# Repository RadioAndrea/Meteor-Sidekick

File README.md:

# Meteor-Sidekick
Slide out keyboard for modern smartphones

Uses Nice!Nano as a microcontroller and the first implementation is sized to a Pixel 7 Pro

Current implementation is with the Kailh Scissor switches as they are very thin and available unlike the ultramecs 6c switches.

If you know of a way to get thinner mechanical switches, like the Ultramecs, at a reasonable price (not $150 a board), please raise an issue in this repo.

# Project Status
## November 2022
Boards that were created were milled with the wrong size of drill bit due to board fab error.
Fabricator remade boards to rectify this.

## January 2023
New boards arrived and components are still being collected.

## Jul 2023
Solder paste stencil arrived and reflow oven was obtained.
Soldering of transistors will happen by paste and reflow, while switches will be done entirely by hand.

## Jan 2024
Board has been produced and now soldered thanks to my steady handed assistant.

# Images
## Real Photographs
### SMD Soldering

### Adding Switches and Caps

### Praise the manufacturing tolerances

## 2D Drawing

## 3D Render
### Front

### Back

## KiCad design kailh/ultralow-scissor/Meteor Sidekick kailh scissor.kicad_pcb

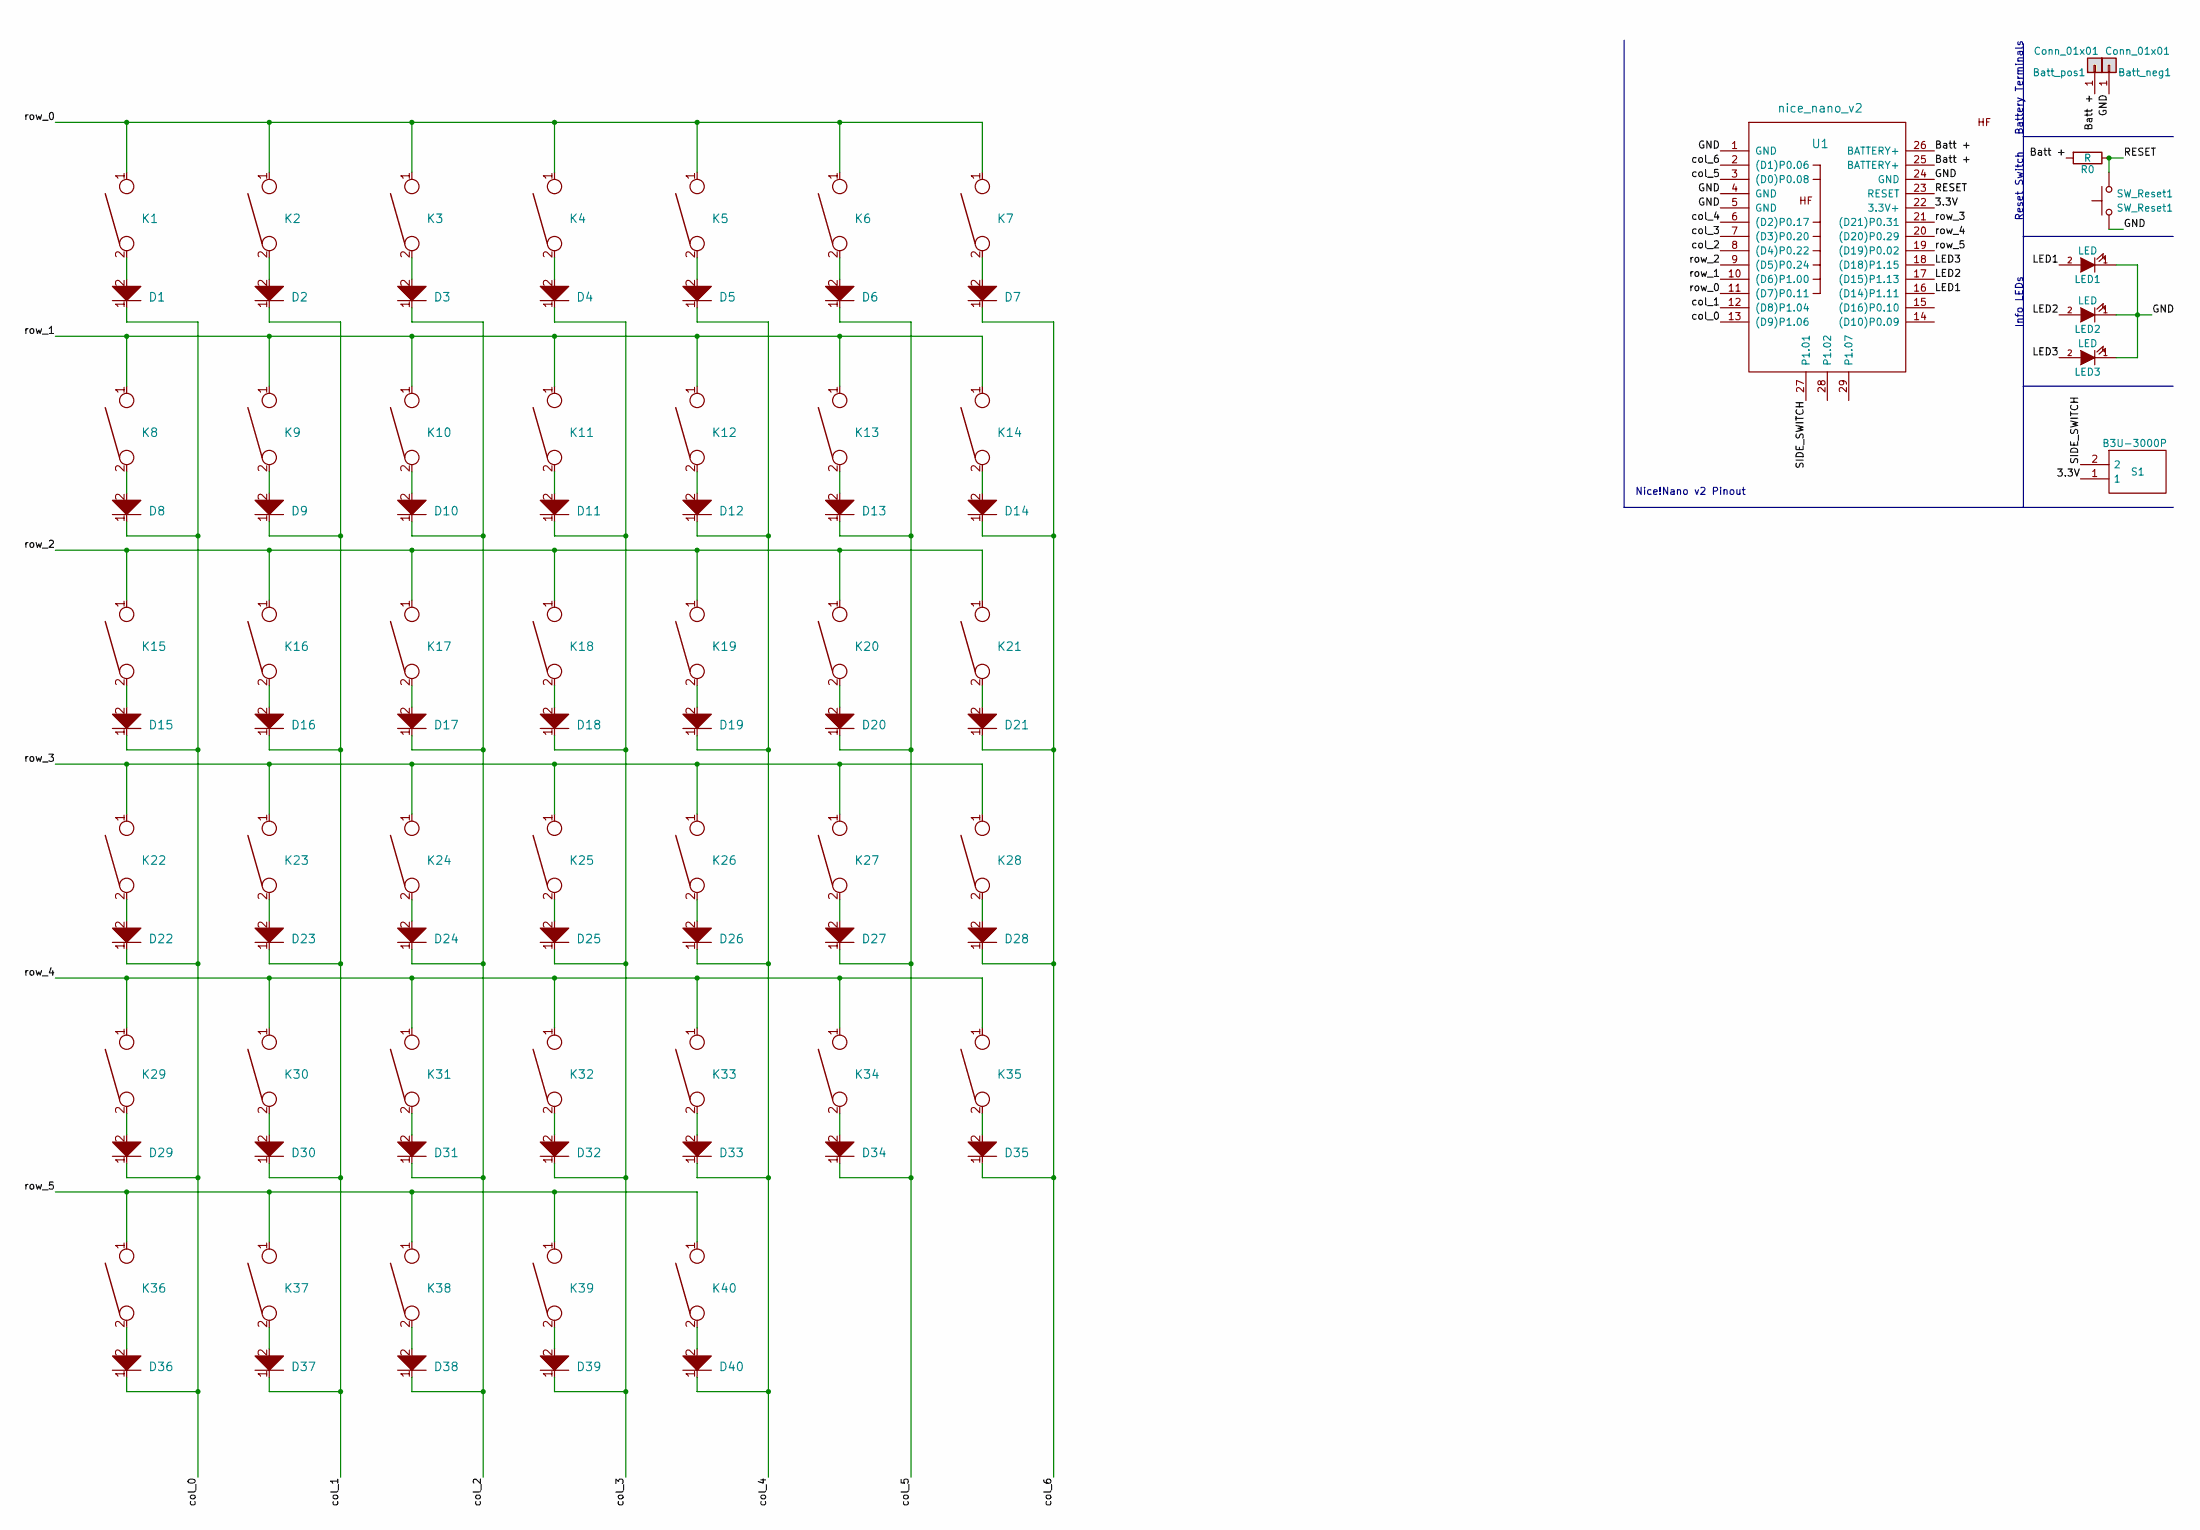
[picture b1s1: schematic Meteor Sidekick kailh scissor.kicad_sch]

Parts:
Batt_neg1: Conn_01x01; SolderWire-0.1sqmm_1x01_D0.4mm_OD1mm
Batt_pos1: Conn_01x01; SolderWire-0.1sqmm_1x01_D0.4mm_OD1mm
D1, D2, D3, D4, D5, D6, D7, D8, D9, D10, D11, D12, D13, D14, D15, D16, D17, D18, D19, D20, D21, D22, D23, D24, D25, D26, D27, D28, D29, D30, D31, D32, D33, D34, D35, D36, D37, D38, D39, D40: D; D_0805_2012Metric
K1, K2, K3, K4, K5, K6, K7, K8, K9, K10, K11, K12, K13, K14, K15, K16, K17, K18, K19, K20, K21, K22, K23, K24, K25, K26, K27, K28, K29, K30, K31, K32, K33, K34, K35, K36, K37, K38, K39, K40: KEYSW; Kailh-PG1425-X-Switch
LED1, LED2, LED3: LED; LED_0805_2012Metric
R0: R; R_0805_2012Metric
S1: B3U-3000P; B3U-1000P; Mouser Part Number 653-B3U-3000P
SW_Reset1: SW_Reset1; SolderJumper-2_P1.3mm_Open_Pad1.0x1.5mm
U1: nice_nano_v2

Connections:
/3.3V: S1.1, U1.22 (3.3V+)
/Batt +: Batt_pos1.1, R0.2, U1.25 (BATTERY+), U1.26 (BATTERY+)
/GND: Batt_neg1.1, LED1.1 (K), LED2.1 (K), LED3.1 (K), SW_Reset1.1, U1.1 (GND), U1.4 (GND), U1.5 (GND), U1.24 (GND)
/LED1: LED1.2 (A), U1.16 ((D14)P1.11)
/LED2: LED2.2 (A), U1.17 ((D15)P1.13)
/LED3: LED3.2 (A), U1.18 ((D18)P1.15)
/RESET: R0.1, SW_Reset1.2, U1.23 (RESET)
/SIDE_SWITCH: S1.2, U1.27 (P1.01)
/col_0: D1.1, D8.1, D15.1, D22.1, D29.1, D36.1, U1.13 ((D9)P1.06)
/col_1: D2.1, D9.1, D16.1, D23.1, D30.1, D37.1, U1.12 ((D8)P1.04)
/col_2: D3.1, D10.1, D17.1, D24.1, D31.1, D38.1, U1.8 ((D4)P0.22)
/col_3: D4.1, D11.1, D18.1, D25.1, D32.1, D39.1, U1.7 ((D3)P0.20)
/col_4: D5.1, D12.1, D19.1, D26.1, D33.1, D40.1, U1.6 ((D2)P0.17)
/col_5: D6.1, D13.1, D20.1, D27.1, D34.1, U1.3 ((D0)P0.08)
/col_6: D7.1, D14.1, D21.1, D28.1, D35.1, U1.2 ((D1)P0.06)
/row_0: K1.1, K2.1, K3.1, K4.1, K5.1, K6.1, K7.1, U1.11 ((D7)P0.11)
/row_1: K8.1, K9.1, K10.1, K11.1, K12.1, K13.1, K14.1, U1.10 ((D6)P1.00)
/row_2: K15.1, K16.1, K17.1, K18.1, K19.1, K20.1, K21.1, U1.9 ((D5)P0.24)
/row_3: K22.1, K23.1, K24.1, K25.1, K26.1, K27.1, K28.1, U1.21 ((D21)P0.31)
/row_4: K29.1, K30.1, K31.1, K32.1, K33.1, K34.1, K35.1, U1.20 ((D20)P0.29)
/row_5: K36.1, K37.1, K38.1, K39.1, K40.1, U1.19 ((D19)P0.02)
unnamed: D1.2, K1.2
unnamed: D2.2, K2.2
unnamed: D3.2, K3.2
unnamed: D4.2, K4.2
unnamed: D5.2, K5.2
unnamed: D6.2, K6.2
unnamed: D7.2, K7.2
unnamed: D8.2, K8.2
unnamed: D9.2, K9.2
unnamed: D10.2, K10.2
unnamed: D11.2, K11.2
unnamed: D12.2, K12.2
unnamed: D13.2, K13.2
unnamed: D14.2, K14.2
unnamed: D15.2, K15.2
unnamed: D16.2, K16.2
unnamed: D17.2, K17.2
unnamed: D18.2, K18.2
unnamed: D19.2, K19.2
unnamed: D20.2, K20.2
unnamed: D21.2, K21.2
unnamed: D22.2, K22.2
unnamed: D23.2, K23.2
unnamed: D24.2, K24.2
unnamed: D25.2, K25.2
unnamed: D26.2, K26.2
unnamed: D27.2, K27.2
unnamed: D28.2, K28.2
unnamed: D29.2, K29.2
unnamed: D30.2, K30.2
unnamed: D31.2, K31.2
unnamed: D32.2, K32.2
unnamed: D33.2, K33.2
unnamed: D34.2, K34.2
unnamed: D35.2, K35.2
unnamed: D36.2, K36.2
unnamed: D37.2, K37.2
unnamed: D38.2, K38.2
unnamed: D39.2, K39.2
unnamed: D40.2, K40.2

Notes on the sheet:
Nice!Nano v2 Pinout
Battery Terminals
Reset Switch
Info LEDs

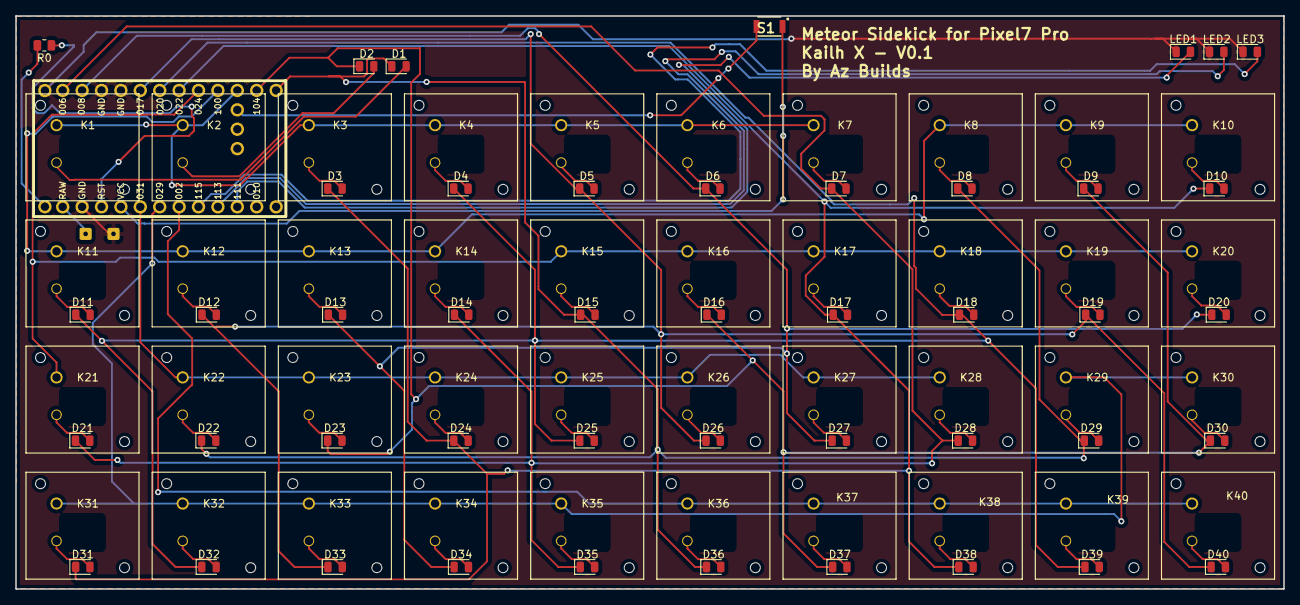
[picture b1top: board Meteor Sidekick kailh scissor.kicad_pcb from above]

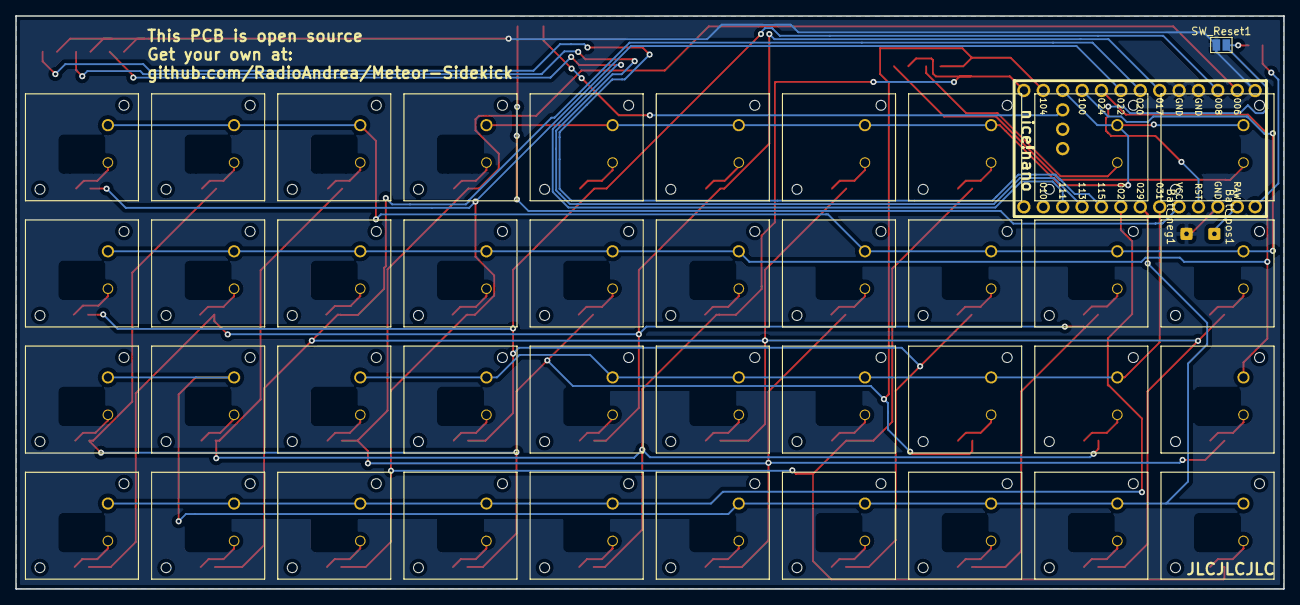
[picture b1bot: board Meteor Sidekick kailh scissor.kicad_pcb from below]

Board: 2 copper layers, 166.0 x 75.0 mm, 89 parts (4 on the bottom side), 61 nets.

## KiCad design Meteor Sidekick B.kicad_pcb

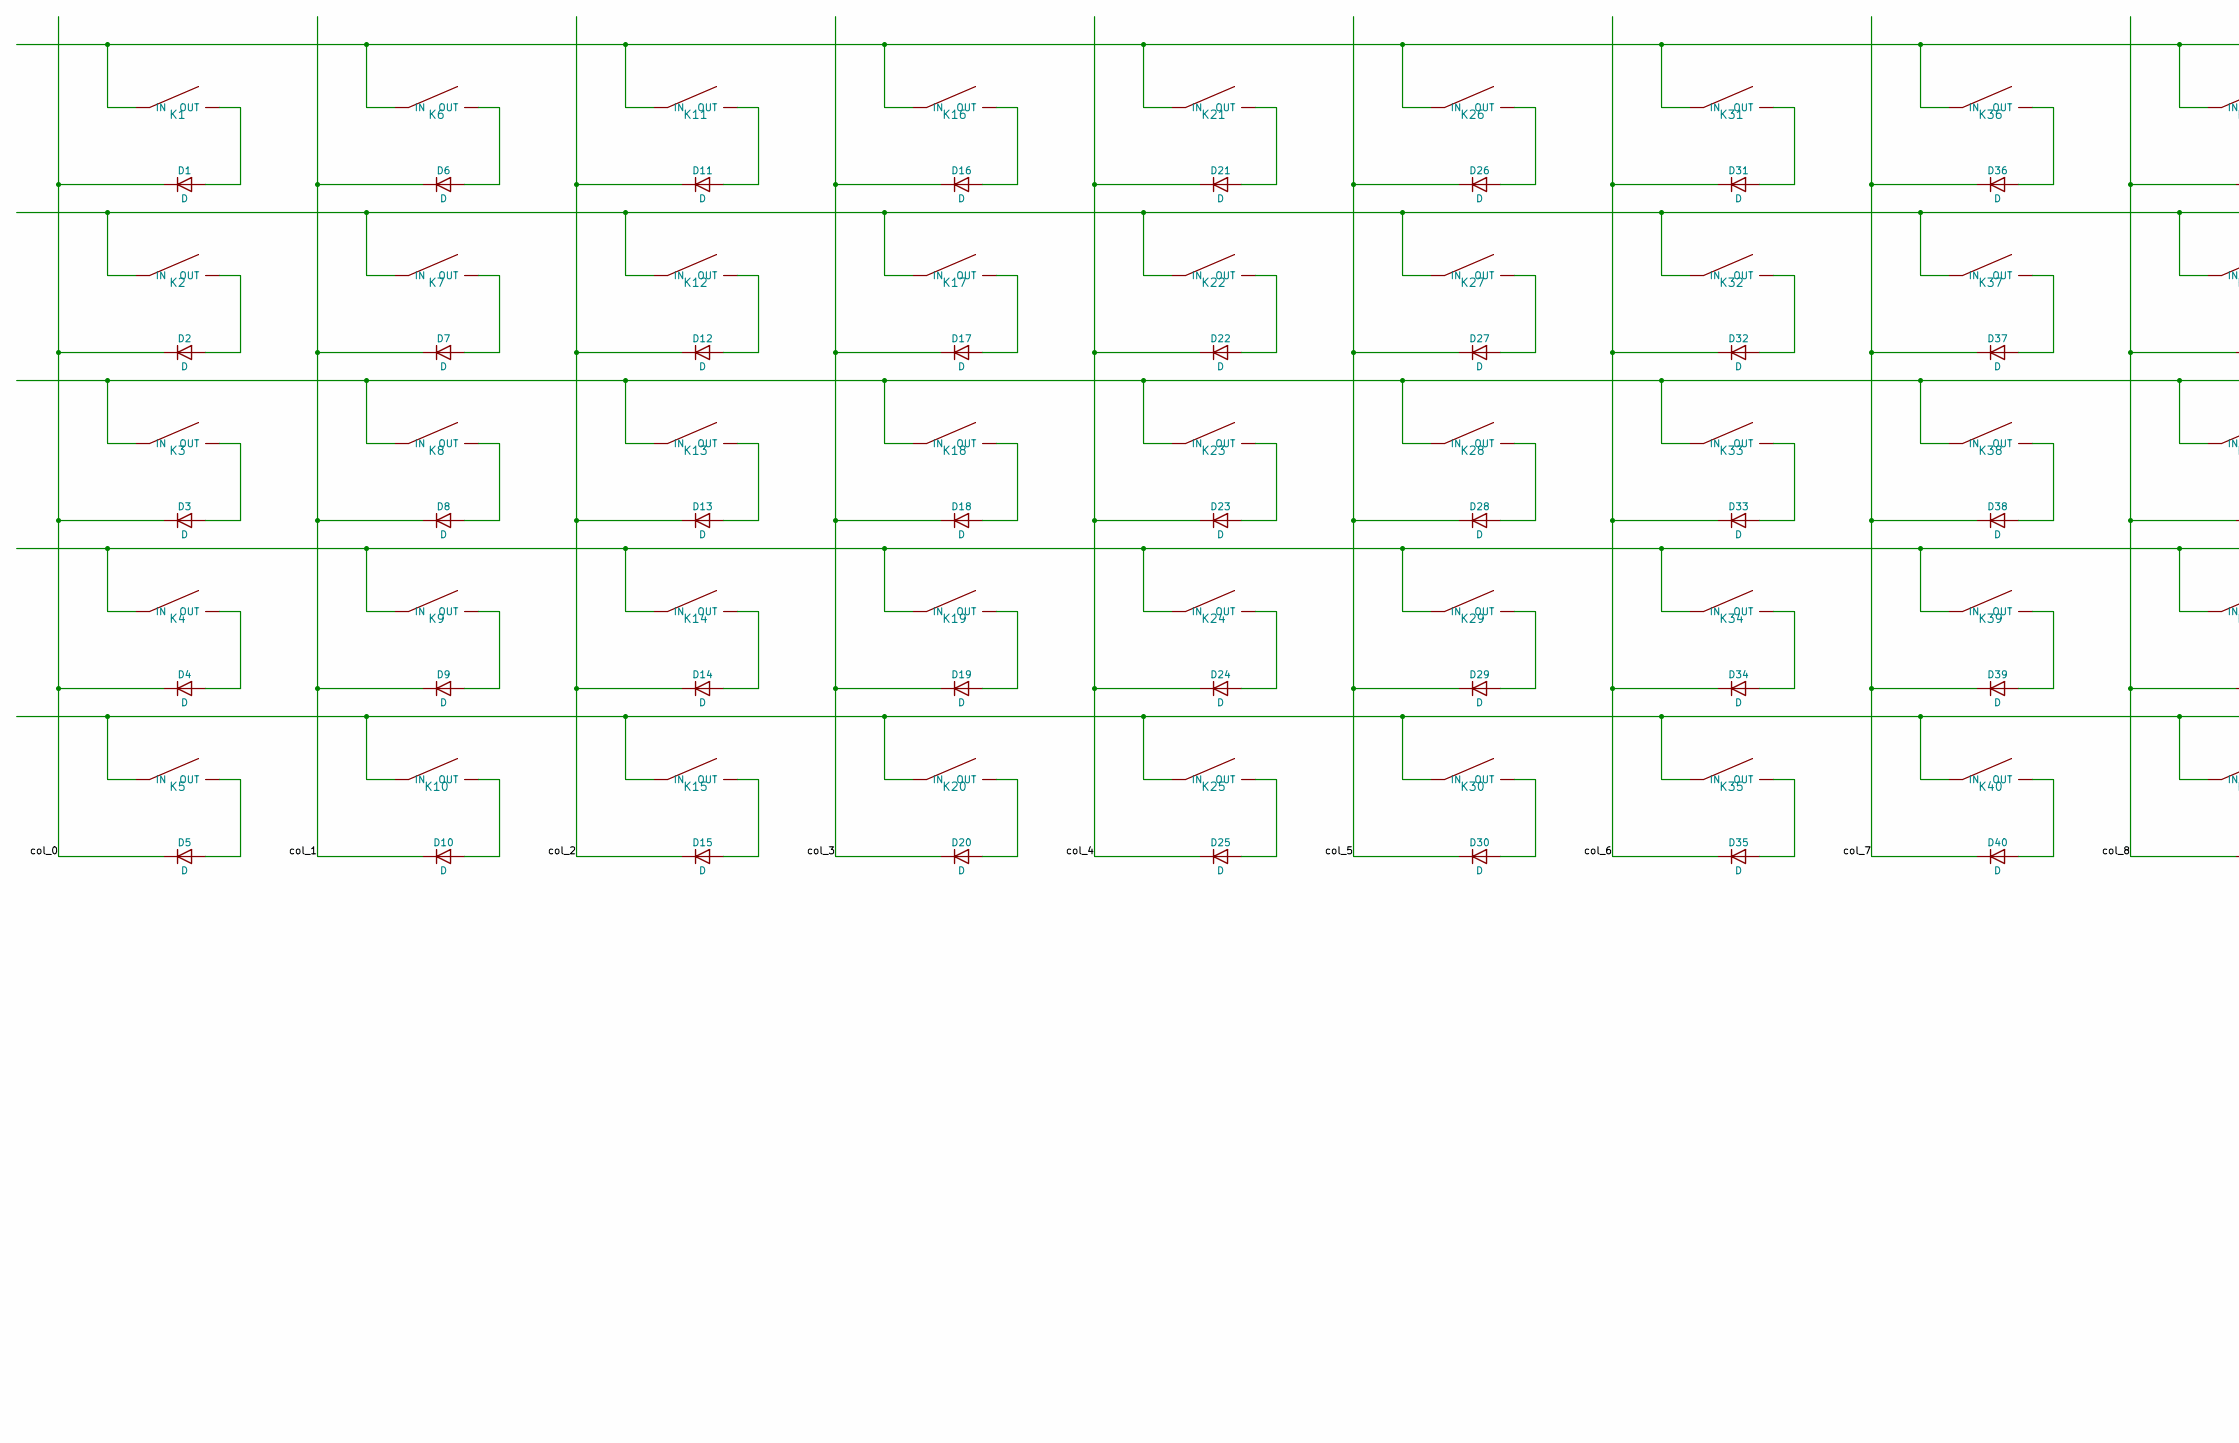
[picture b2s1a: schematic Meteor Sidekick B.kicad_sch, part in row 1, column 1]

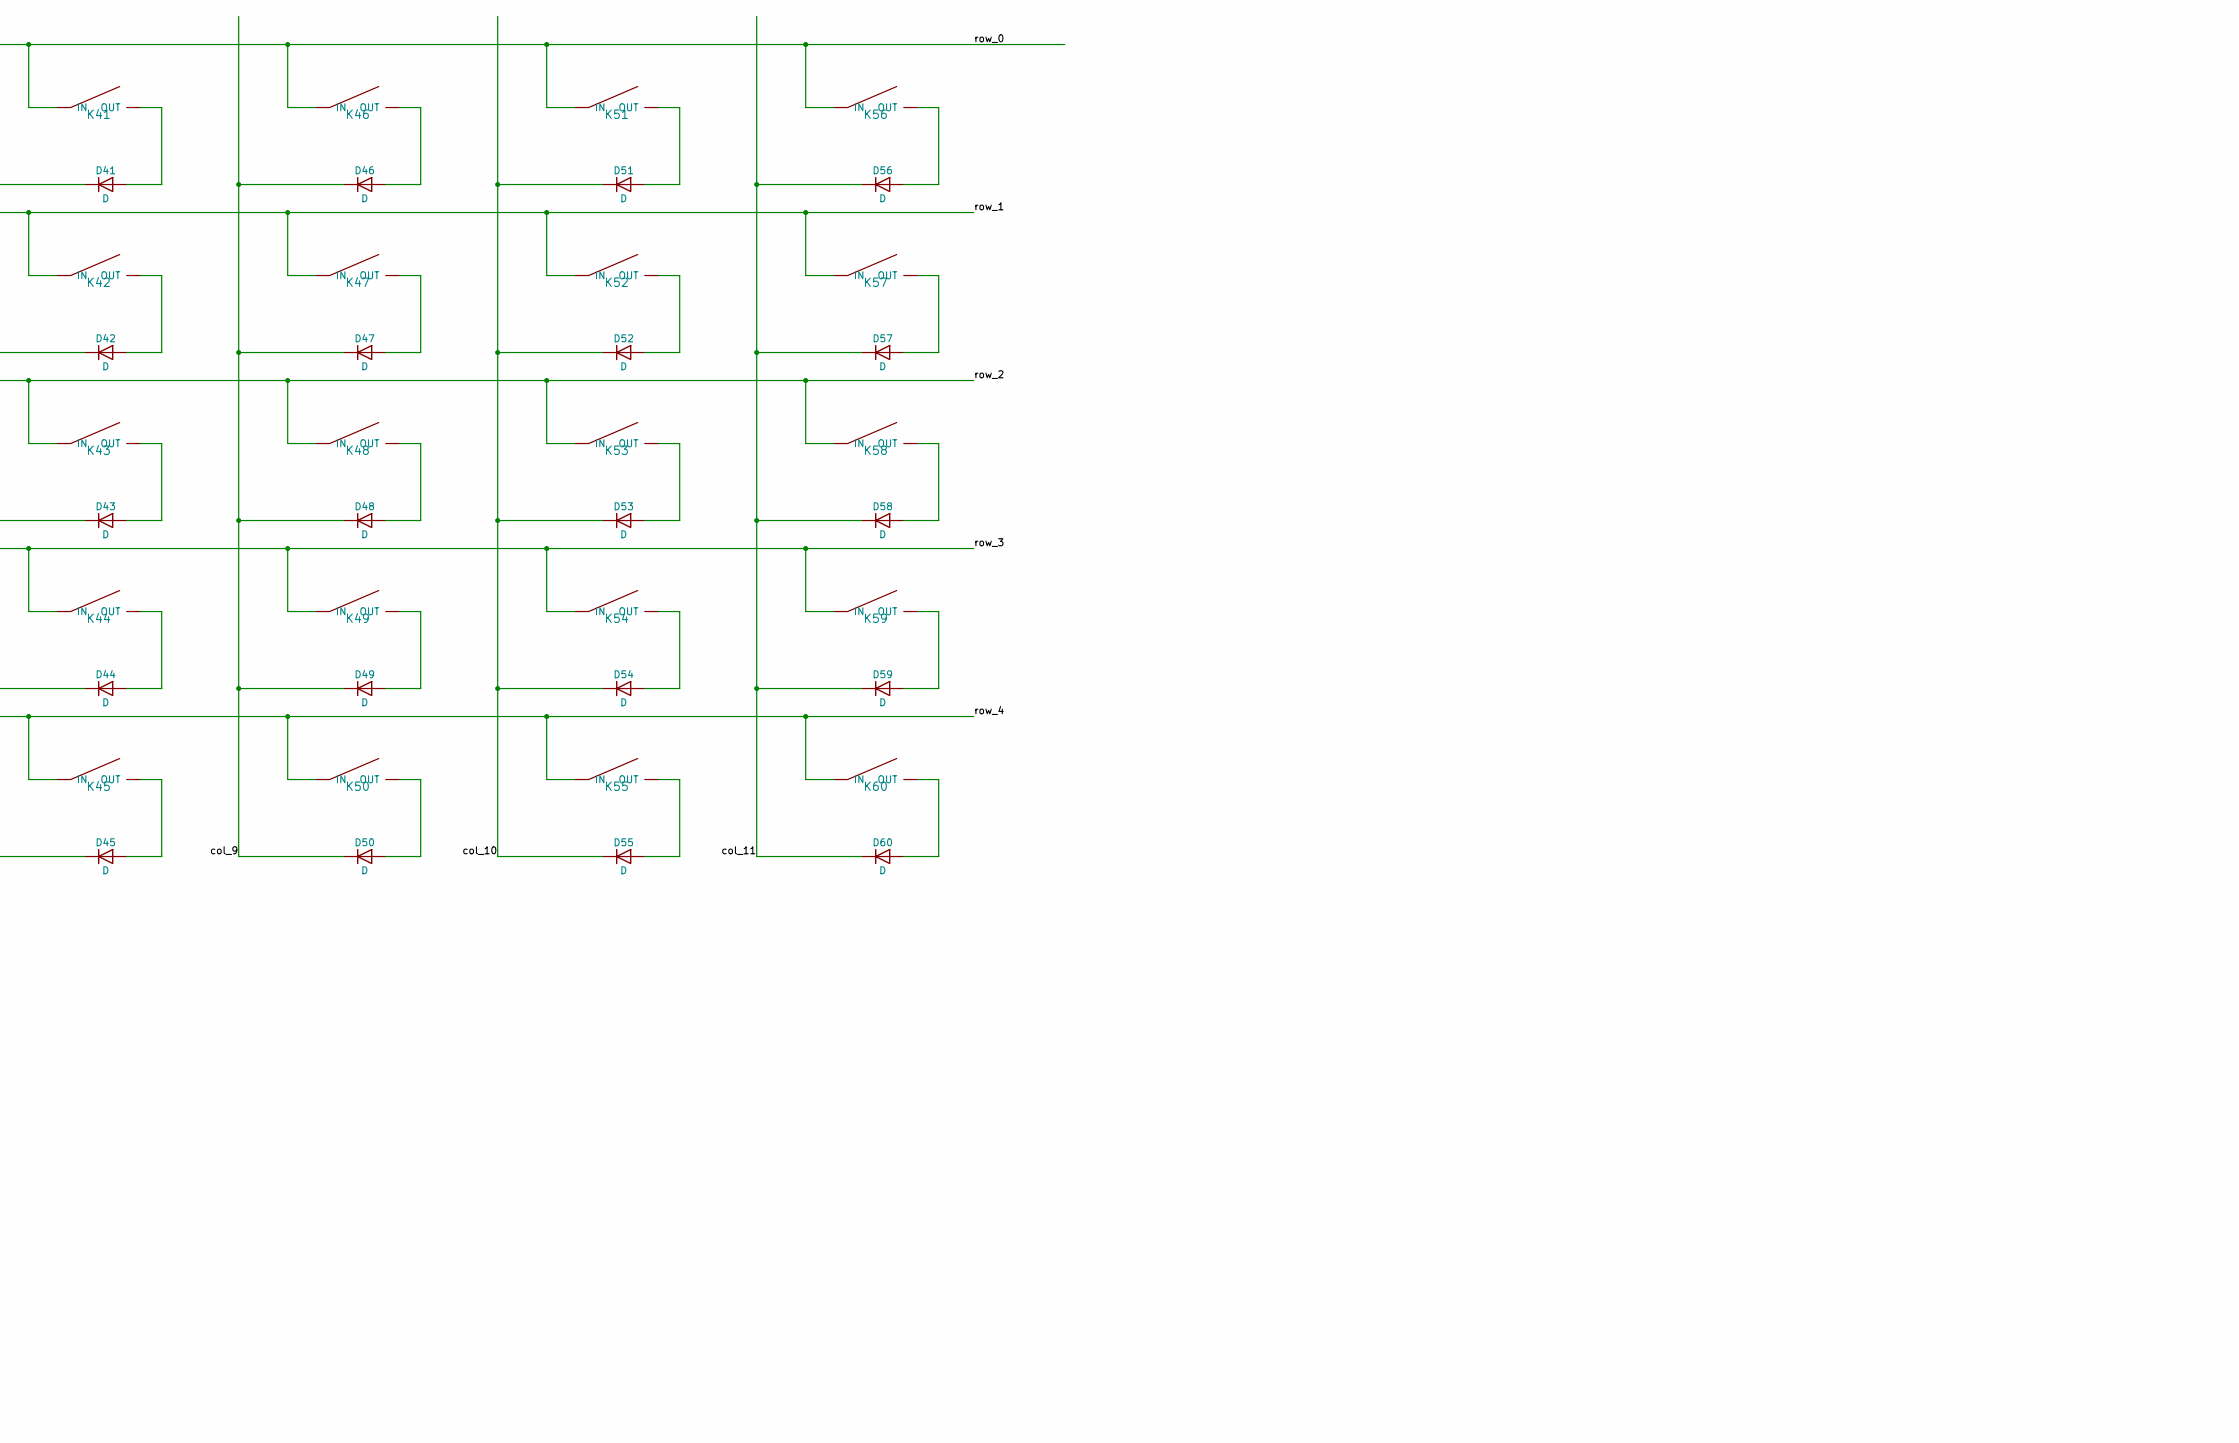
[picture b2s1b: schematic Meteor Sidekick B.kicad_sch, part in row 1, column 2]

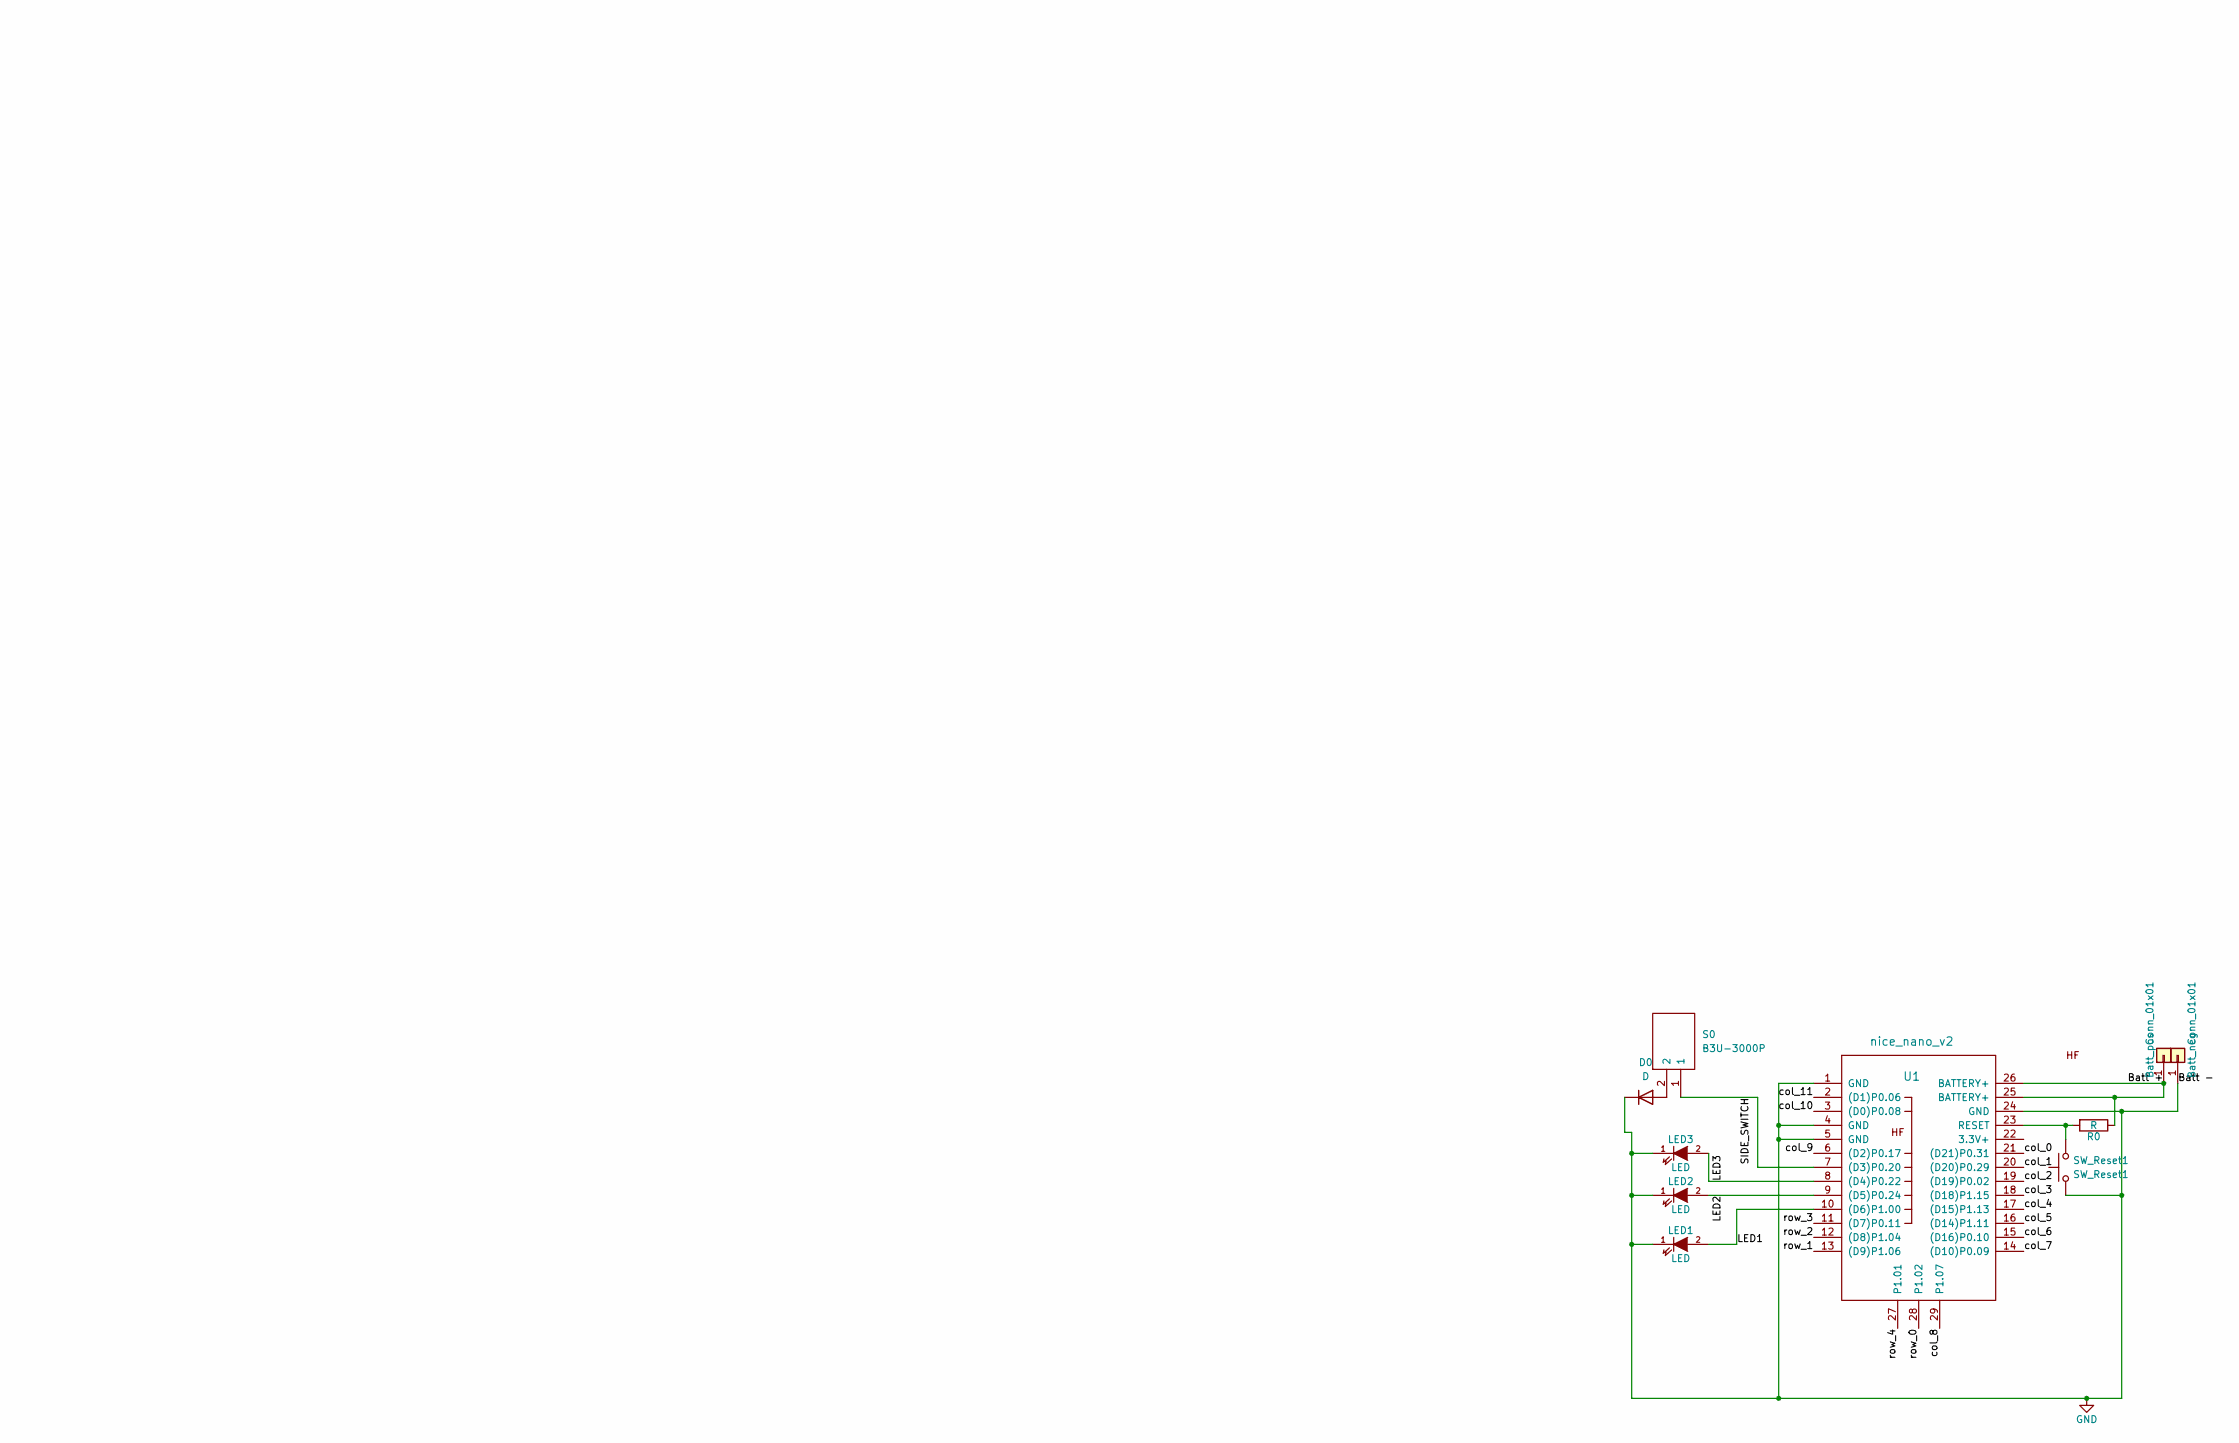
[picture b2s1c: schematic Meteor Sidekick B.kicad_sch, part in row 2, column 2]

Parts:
Batt_neg: Conn_01x01; SolderWire-0.1sqmm_1x01_D0.4mm_OD1mm
Batt_pos: Conn_01x01; SolderWire-0.1sqmm_1x01_D0.4mm_OD1mm
D0, D1, D2, D3, D4, D5, D6, D7, D8, D9, D10, D11, D12, D13, D14, D15, D16, D17, D18, D19, D20, D21, D22, D23, D24, D25, D26, D27, D28, D29, D30, D31, D32, D33, D34, D35, D36, D37, D38, D39, D40, D41, D42, D43, D44, D45, D46, D47, D48, D49, D50, D51, D52, D53, D54, D55, D56, D57, D58, D59, D60: D; D_0805_2012Metric
K1, K2, K3, K4, K5, K6, K7, K8, K9, K10, K11, K12, K13, K14, K15, K16, K17, K18, K19, K20, K21, K22, K23, K24, K25, K26, K27, K28, K29, K30, K31, K32, K33, K34, K35, K36, K37, K38, K39, K40, K41, K42, K43, K44, K45, K46, K47, K48, K49, K50, K51, K52, K53, K54, K55, K56, K57, K58, K59, K60: KEYSW_10; 6CJ1N0PR
LED1, LED2, LED3: LED; LED_0805_2012Metric
R0: R; R_0805_2012Metric
S0: B3U-3000P; B3U-1000P; Mouser Part Number 653-B3U-3000P
SW_Reset1: SW_Reset1; SolderJumper-2_P1.3mm_Open_Pad1.0x1.5mm
U1: nice_nano_v2

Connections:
/Batt +: Batt_pos.1, R0.1, U1.25 (BATTERY+), U1.26 (BATTERY+)
/LED1: LED1.2 (A), U1.10 ((D6)P1.00)
/LED2: LED2.2 (A), U1.9 ((D5)P0.24)
/LED3: LED3.2 (A), U1.8 ((D4)P0.22)
/SIDE_SWITCH: S0.1, U1.7 ((D3)P0.20)
/col_0: D1.1 (K), D2.1 (K), D3.1 (K), D4.1 (K), D5.1 (K), U1.21 ((D21)P0.31)
/col_1: D6.1 (K), D7.1 (K), D8.1 (K), D9.1 (K), D10.1 (K), U1.20 ((D20)P0.29)
/col_2: D11.1 (K), D12.1 (K), D13.1 (K), D14.1 (K), D15.1 (K), U1.19 ((D19)P0.02)
/col_3: D16.1 (K), D17.1 (K), D18.1 (K), D19.1 (K), D20.1 (K), U1.18 ((D18)P1.15)
/col_4: D21.1 (K), D22.1 (K), D23.1 (K), D24.1 (K), D25.1 (K), U1.17 ((D15)P1.13)
/col_5: D26.1 (K), D27.1 (K), D28.1 (K), D29.1 (K), D30.1 (K), U1.16 ((D14)P1.11)
/col_6: D31.1 (K), D32.1 (K), D33.1 (K), D34.1 (K), D35.1 (K), U1.15 ((D16)P0.10)
/col_7: D36.1 (K), D37.1 (K), D38.1 (K), D39.1 (K), D40.1 (K), U1.14 ((D10)P0.09)
/col_8: D41.1 (K), D42.1 (K), D43.1 (K), D44.1 (K), D45.1 (K), U1.29 (P1.07)
/col_9: D46.1 (K), D47.1 (K), D48.1 (K), D49.1 (K), D50.1 (K), U1.6 ((D2)P0.17)
/col_10: D51.1 (K), D52.1 (K), D53.1 (K), D54.1 (K), D55.1 (K), U1.3 ((D0)P0.08)
/col_11: D56.1 (K), D57.1 (K), D58.1 (K), D59.1 (K), D60.1 (K), U1.2 ((D1)P0.06)
/row_0: K1.3 (IN), K1.4 (IN), K1.7 (IN), K1.8 (IN), K6.3 (IN), K6.4 (IN), K6.7 (IN), K6.8 (IN), K11.3 (IN), K11.4 (IN), K11.7 (IN), K11.8 (IN), K16.3 (IN), K16.4 (IN), K16.7 (IN), K16.8 (IN), K21.3 (IN), K21.4 (IN), K21.7 (IN), K21.8 (IN), K26.3 (IN), K26.4 (IN), K26.7 (IN), K26.8 (IN), K31.3 (IN), K31.4 (IN), K31.7 (IN), K31.8 (IN), K36.3 (IN), K36.4 (IN), K36.7 (IN), K36.8 (IN), K41.3 (IN), K41.4 (IN), K41.7 (IN), K41.8 (IN), K46.3 (IN), K46.4 (IN), K46.7 (IN), K46.8 (IN), K51.3 (IN), K51.4 (IN), K51.7 (IN), K51.8 (IN), K56.3 (IN), K56.4 (IN), K56.7 (IN), K56.8 (IN), U1.28 (P1.02)
/row_1: K2.3 (IN), K2.4 (IN), K2.7 (IN), K2.8 (IN), K7.3 (IN), K7.4 (IN), K7.7 (IN), K7.8 (IN), K12.3 (IN), K12.4 (IN), K12.7 (IN), K12.8 (IN), K17.3 (IN), K17.4 (IN), K17.7 (IN), K17.8 (IN), K22.3 (IN), K22.4 (IN), K22.7 (IN), K22.8 (IN), K27.3 (IN), K27.4 (IN), K27.7 (IN), K27.8 (IN), K32.3 (IN), K32.4 (IN), K32.7 (IN), K32.8 (IN), K37.3 (IN), K37.4 (IN), K37.7 (IN), K37.8 (IN), K42.3 (IN), K42.4 (IN), K42.7 (IN), K42.8 (IN), K47.3 (IN), K47.4 (IN), K47.7 (IN), K47.8 (IN), K52.3 (IN), K52.4 (IN), K52.7 (IN), K52.8 (IN), K57.3 (IN), K57.4 (IN), K57.7 (IN), K57.8 (IN), U1.13 ((D9)P1.06)
/row_2: K3.3 (IN), K3.4 (IN), K3.7 (IN), K3.8 (IN), K8.3 (IN), K8.4 (IN), K8.7 (IN), K8.8 (IN), K13.3 (IN), K13.4 (IN), K13.7 (IN), K13.8 (IN), K18.3 (IN), K18.4 (IN), K18.7 (IN), K18.8 (IN), K23.3 (IN), K23.4 (IN), K23.7 (IN), K23.8 (IN), K28.3 (IN), K28.4 (IN), K28.7 (IN), K28.8 (IN), K33.3 (IN), K33.4 (IN), K33.7 (IN), K33.8 (IN), K38.3 (IN), K38.4 (IN), K38.7 (IN), K38.8 (IN), K43.3 (IN), K43.4 (IN), K43.7 (IN), K43.8 (IN), K48.3 (IN), K48.4 (IN), K48.7 (IN), K48.8 (IN), K53.3 (IN), K53.4 (IN), K53.7 (IN), K53.8 (IN), K58.3 (IN), K58.4 (IN), K58.7 (IN), K58.8 (IN), U1.12 ((D8)P1.04)
/row_3: K4.3 (IN), K4.4 (IN), K4.7 (IN), K4.8 (IN), K9.3 (IN), K9.4 (IN), K9.7 (IN), K9.8 (IN), K14.3 (IN), K14.4 (IN), K14.7 (IN), K14.8 (IN), K19.3 (IN), K19.4 (IN), K19.7 (IN), K19.8 (IN), K24.3 (IN), K24.4 (IN), K24.7 (IN), K24.8 (IN), K29.3 (IN), K29.4 (IN), K29.7 (IN), K29.8 (IN), K34.3 (IN), K34.4 (IN), K34.7 (IN), K34.8 (IN), K39.3 (IN), K39.4 (IN), K39.7 (IN), K39.8 (IN), K44.3 (IN), K44.4 (IN), K44.7 (IN), K44.8 (IN), K49.3 (IN), K49.4 (IN), K49.7 (IN), K49.8 (IN), K54.3 (IN), K54.4 (IN), K54.7 (IN), K54.8 (IN), K59.3 (IN), K59.4 (IN), K59.7 (IN), K59.8 (IN), U1.11 ((D7)P0.11)
/row_4: K5.3 (IN), K5.4 (IN), K5.7 (IN), K5.8 (IN), K10.3 (IN), K10.4 (IN), K10.7 (IN), K10.8 (IN), K15.3 (IN), K15.4 (IN), K15.7 (IN), K15.8 (IN), K20.3 (IN), K20.4 (IN), K20.7 (IN), K20.8 (IN), K25.3 (IN), K25.4 (IN), K25.7 (IN), K25.8 (IN), K30.3 (IN), K30.4 (IN), K30.7 (IN), K30.8 (IN), K35.3 (IN), K35.4 (IN), K35.7 (IN), K35.8 (IN), K40.3 (IN), K40.4 (IN), K40.7 (IN), K40.8 (IN), K45.3 (IN), K45.4 (IN), K45.7 (IN), K45.8 (IN), K50.3 (IN), K50.4 (IN), K50.7 (IN), K50.8 (IN), K55.3 (IN), K55.4 (IN), K55.7 (IN), K55.8 (IN), K60.3 (IN), K60.4 (IN), K60.7 (IN), K60.8 (IN), U1.27 (P1.01)
GND: Batt_neg.1, D0.1 (K), LED1.1 (K), LED2.1 (K), LED3.1 (K), SW_Reset1.1, U1.1 (GND), U1.4 (GND), U1.5 (GND), U1.24 (GND); also elsewhere on the board
unnamed: D0.2 (A), S0.2
unnamed: D1.2 (A), K1.5 (OUT), K1.6 (OUT)
unnamed: D2.2 (A), K2.5 (OUT), K2.6 (OUT)
unnamed: D3.2 (A), K3.5 (OUT), K3.6 (OUT)
unnamed: D4.2 (A), K4.5 (OUT), K4.6 (OUT)
unnamed: D5.2 (A), K5.5 (OUT), K5.6 (OUT)
unnamed: D6.2 (A), K6.5 (OUT), K6.6 (OUT)
unnamed: D7.2 (A), K7.5 (OUT), K7.6 (OUT)
unnamed: D8.2 (A), K8.5 (OUT), K8.6 (OUT)
unnamed: D9.2 (A), K9.5 (OUT), K9.6 (OUT)
unnamed: D10.2 (A), K10.5 (OUT), K10.6 (OUT)
unnamed: D11.2 (A), K11.5 (OUT), K11.6 (OUT)
unnamed: D12.2 (A), K12.5 (OUT), K12.6 (OUT)
unnamed: D13.2 (A), K13.5 (OUT), K13.6 (OUT)
unnamed: D14.2 (A), K14.5 (OUT), K14.6 (OUT)
unnamed: D15.2 (A), K15.5 (OUT), K15.6 (OUT)
unnamed: D16.2 (A), K16.5 (OUT), K16.6 (OUT)
unnamed: D17.2 (A), K17.5 (OUT), K17.6 (OUT)
unnamed: D18.2 (A), K18.5 (OUT), K18.6 (OUT)
unnamed: D19.2 (A), K19.5 (OUT), K19.6 (OUT)
unnamed: D20.2 (A), K20.5 (OUT), K20.6 (OUT)
unnamed: D21.2 (A), K21.5 (OUT), K21.6 (OUT)
unnamed: D22.2 (A), K22.5 (OUT), K22.6 (OUT)
unnamed: D23.2 (A), K23.5 (OUT), K23.6 (OUT)
unnamed: D24.2 (A), K24.5 (OUT), K24.6 (OUT)
unnamed: D25.2 (A), K25.5 (OUT), K25.6 (OUT)
unnamed: D26.2 (A), K26.5 (OUT), K26.6 (OUT)
unnamed: D27.2 (A), K27.5 (OUT), K27.6 (OUT)
unnamed: D28.2 (A), K28.5 (OUT), K28.6 (OUT)
unnamed: D29.2 (A), K29.5 (OUT), K29.6 (OUT)
unnamed: D30.2 (A), K30.5 (OUT), K30.6 (OUT)
unnamed: D31.2 (A), K31.5 (OUT), K31.6 (OUT)
unnamed: D32.2 (A), K32.5 (OUT), K32.6 (OUT)
unnamed: D33.2 (A), K33.5 (OUT), K33.6 (OUT)
unnamed: D34.2 (A), K34.5 (OUT), K34.6 (OUT)
unnamed: D35.2 (A), K35.5 (OUT), K35.6 (OUT)
unnamed: D36.2 (A), K36.5 (OUT), K36.6 (OUT)
unnamed: D37.2 (A), K37.5 (OUT), K37.6 (OUT)
unnamed: D38.2 (A), K38.5 (OUT), K38.6 (OUT)
unnamed: D39.2 (A), K39.5 (OUT), K39.6 (OUT)
unnamed: D40.2 (A), K40.5 (OUT), K40.6 (OUT)
unnamed: D41.2 (A), K41.5 (OUT), K41.6 (OUT)
unnamed: D42.2 (A), K42.5 (OUT), K42.6 (OUT)
unnamed: D43.2 (A), K43.5 (OUT), K43.6 (OUT)
unnamed: D44.2 (A), K44.5 (OUT), K44.6 (OUT)
unnamed: D45.2 (A), K45.5 (OUT), K45.6 (OUT)
unnamed: D46.2 (A), K46.5 (OUT), K46.6 (OUT)
unnamed: D47.2 (A), K47.5 (OUT), K47.6 (OUT)
unnamed: D48.2 (A), K48.5 (OUT), K48.6 (OUT)
unnamed: D49.2 (A), K49.5 (OUT), K49.6 (OUT)
unnamed: D50.2 (A), K50.5 (OUT), K50.6 (OUT)
unnamed: D51.2 (A), K51.5 (OUT), K51.6 (OUT)
unnamed: D52.2 (A), K52.5 (OUT), K52.6 (OUT)
unnamed: D53.2 (A), K53.5 (OUT), K53.6 (OUT)
unnamed: D54.2 (A), K54.5 (OUT), K54.6 (OUT)
unnamed: D55.2 (A), K55.5 (OUT), K55.6 (OUT)
unnamed: D56.2 (A), K56.5 (OUT), K56.6 (OUT)
unnamed: D57.2 (A), K57.5 (OUT), K57.6 (OUT)
unnamed: D58.2 (A), K58.5 (OUT), K58.6 (OUT)
unnamed: D59.2 (A), K59.5 (OUT), K59.6 (OUT)
unnamed: D60.2 (A), K60.5 (OUT), K60.6 (OUT)
unnamed 84: R0.2, SW_Reset1.2, U1.23 (RESET); also elsewhere on the board
